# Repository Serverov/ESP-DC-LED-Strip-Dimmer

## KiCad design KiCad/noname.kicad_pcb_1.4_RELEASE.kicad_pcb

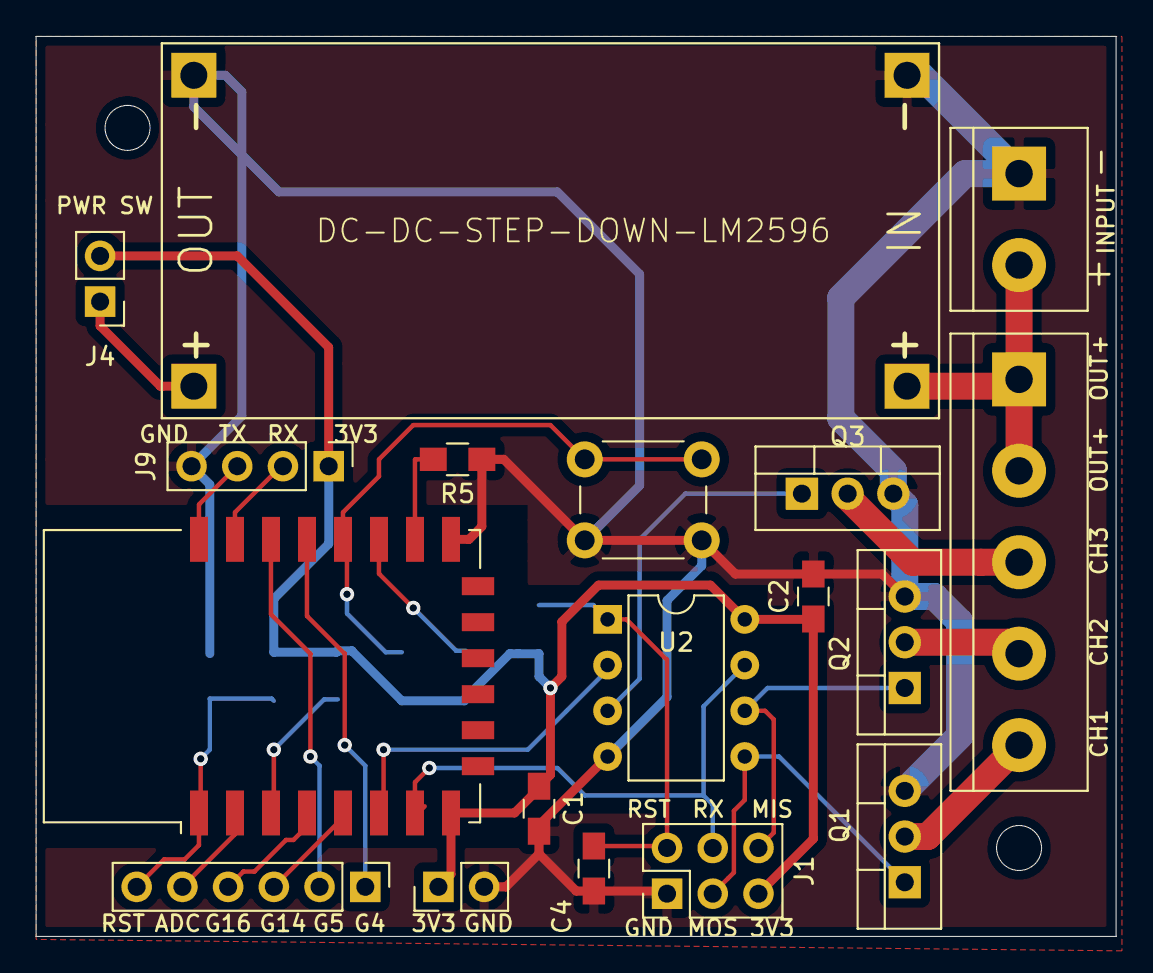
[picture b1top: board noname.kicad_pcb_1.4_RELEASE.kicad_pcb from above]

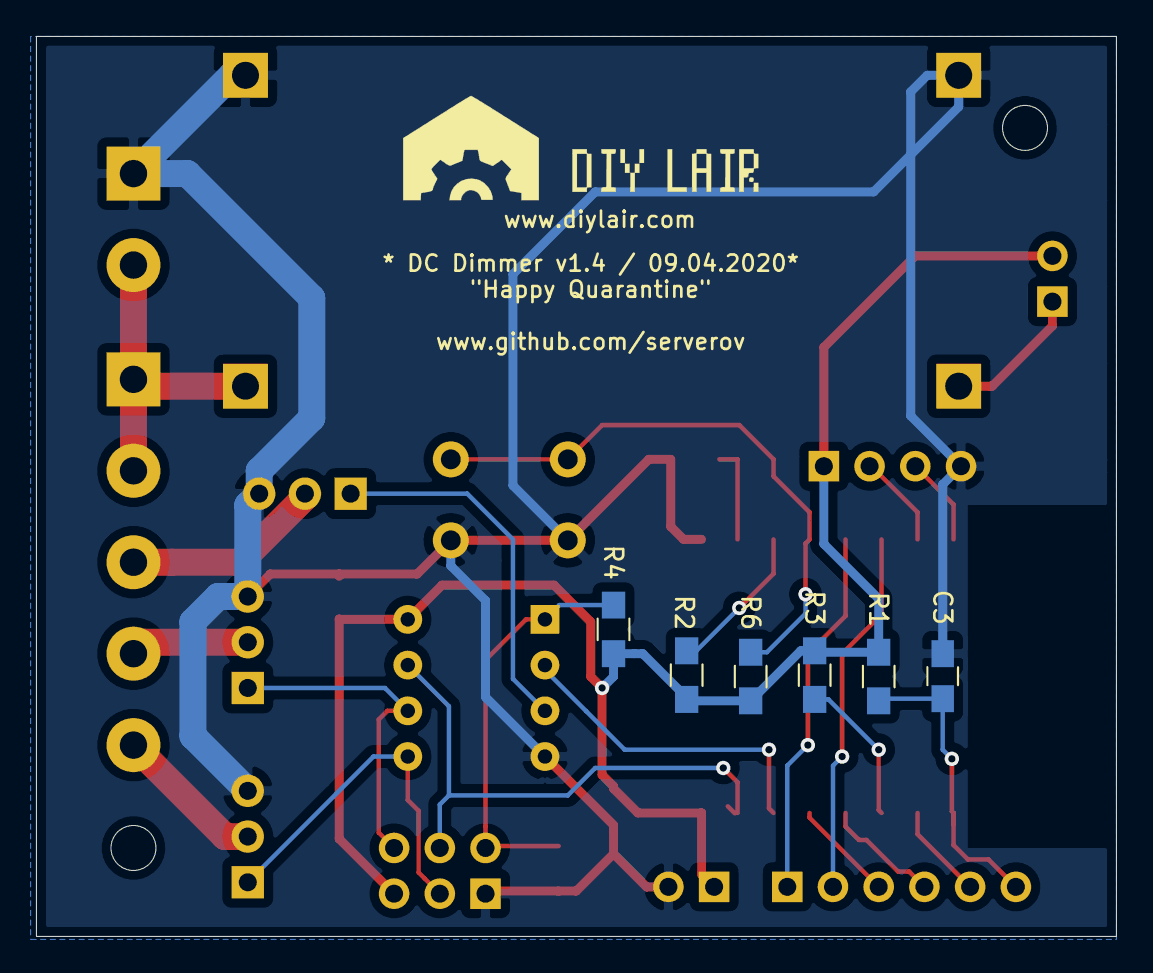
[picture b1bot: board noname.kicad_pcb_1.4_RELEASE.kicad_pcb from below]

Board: 2 copper layers, 60.0 x 50.0 mm, 24 parts (6 on the bottom side), 25 nets.

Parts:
C1, C2: 0.1; C_0805_HandSoldering
C3, C4: 470pF; C_0805_HandSoldering
DIY1: DC-DC-STEP-DOWN-LM2596; diy-modules-DC-DC-STEP-DOWN-LM2596NOHOLE
J1: Conn_02x03_Odd_Even; Pin_Header_Straight_2x03_Pitch2.54mm
J2: Screw_Terminal_01x05; TerminalBlock_bornier-5_P5.08mm
J3: DC IN; TerminalBlock_bornier-2_P5.08mm
J4: Conn_01x02; Pin_Header_Straight_1x02_Pitch2.54mm
J7: pwr; Pin_Header_Straight_1x02_Pitch2.54mm
J9: Conn_01x04; Pin_Header_Straight_1x04_Pitch2.54mm
J10: Conn_01x06; Pin_Header_Straight_1x06_Pitch2.54mm
Q1, Q2, Q3: IRLB8721PBF; TO-220-3_Vertical
R1, R2, R3, R4, R5, R6: 10K; R_0805_HandSoldering
SW1: SW_Push; SW_PUSH_6mm
U1: ESP-12E
U2: ATtiny85-20PU; DIP-8_W7.62mm

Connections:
+3V3: C1.1, C2.1, J1.5, J4.2, J7.1, J9.1, R1.1, R2.2, R3.2, R4.1, R6.2, U1.8, U2.8
+24V: DIY1.IN+, J2.1, J2.2, J3.2
/A-RST: C4.1, J1.2, R4.2, U2.1
/ADC: J10.5, U1.2
/CH1\MOSI: J1.3, Q1.1, U2.5
/CH2\MISO: J1.6, Q2.1, U2.6
/CH3: Q3.1, U2.3
/E-EN: R3.1, U1.3
/E-GPIO0: R6.1, SW1.1, U1.18
/E-GPIO1\TX: J9.3, U1.22
/E-GPIO2: R2.1, U1.17
/E-GPIO3\RX: J9.2, U1.21
/E-GPIO4: J10.1, U1.19
/E-GPIO5: J10.2, U1.20
/E-GPIO14: J10.3, U1.5
/E-GPIO15: R5.1, U1.16
/E-GPIO16: J10.4, U1.4
/E-RST: C3.1, J10.6, R1.2, U1.1
/RX\SCK: J1.4, U1.7, U2.7
/TX: U1.6, U2.2
GND: C1.2, C2.2, C3.2, C4.2, DIY1.IN-, DIY1.OUT-, J1.1, J3.1, J7.2, J9.4, Q1.3, Q2.3, Q3.3, R5.2, SW1.2, U1.15, U2.4
unnamed: DIY1.OUT+, J4.1
unnamed: J2.3, Q3.2
unnamed: J2.4, Q2.2
unnamed: J2.5, Q1.2

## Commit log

2020-06-03 1
    1
